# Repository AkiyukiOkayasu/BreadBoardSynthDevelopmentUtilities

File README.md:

# BreadBoardSynthDevelopmentUtilities  
[ブレッドボード　６穴版　ＥＩＣ－３９０１](https://akizukidenshi.com/catalog/g/gP-12366/)

## Eurorack power  
Pull the Eurorack's power bus cable out to the BreadBoard's power rail.  
Only split power lines in the middle can be used.  

## Pod

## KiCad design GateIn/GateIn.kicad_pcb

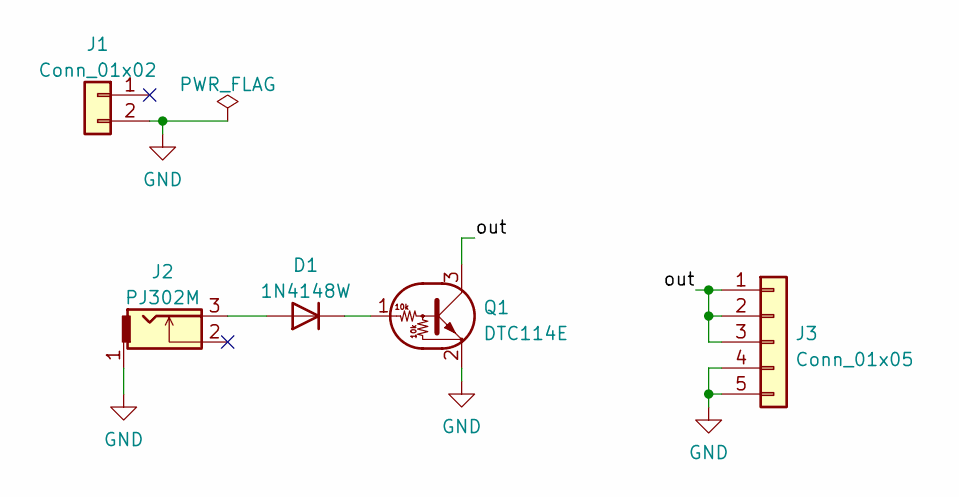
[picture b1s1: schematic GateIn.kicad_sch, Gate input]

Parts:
D1: 1N4148W; D_SOD-123
J1: Conn_01x02; PinHeader_1x02_P2.54mm_Vertical
J2: PJ302M
J3: Conn_01x05; PinHeader_1x05_P2.54mm_Vertical
Q1: DTC114E; SC-59_Handsoldering

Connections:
/out: J3.1, J3.2, J3.3, Q1.3 (C)
GND: J1.2, J2.1, J3.4, J3.5, Q1.2 (E)
unnamed: D1.1 (K), Q1.1 (B)
unnamed: D1.2 (A), J2.3

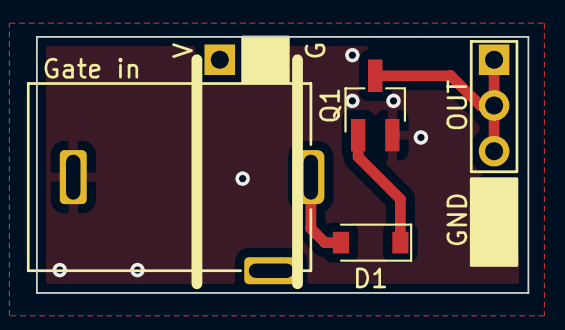
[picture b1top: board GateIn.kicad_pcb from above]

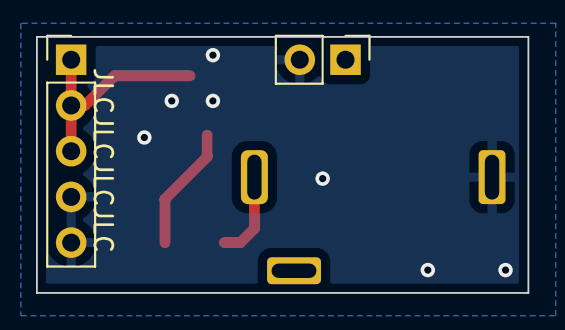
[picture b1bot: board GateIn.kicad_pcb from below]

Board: 2 copper layers, 27.3 x 14.2 mm, 5 parts (2 on the bottom side), 4 nets.

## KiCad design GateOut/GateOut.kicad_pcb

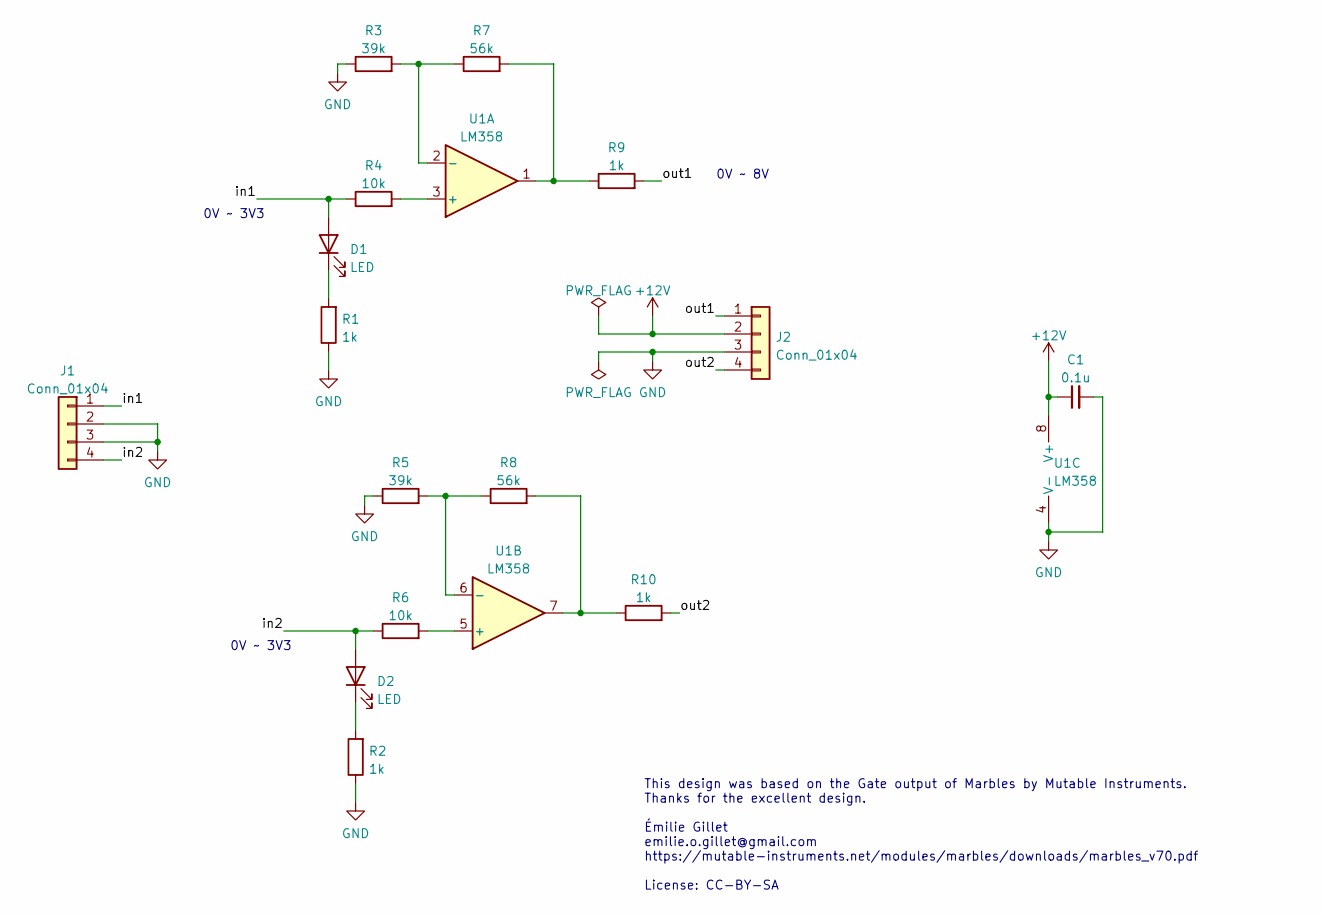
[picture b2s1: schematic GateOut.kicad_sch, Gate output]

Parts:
C1: 0.1u; C_0402_1005Metric_Pad0.74x0.62mm_HandSolder
D1, D2: LED; LED_0402_1005Metric_Pad0.77x0.64mm_HandSolder
J1, J2: Conn_01x04; PinHeader_1x04_P2.54mm_Vertical
R1, R2, R9, R10: 1k; R_0402_1005Metric_Pad0.72x0.64mm_HandSolder
R3, R5: 39k; R_0402_1005Metric_Pad0.72x0.64mm_HandSolder
R4, R6: 10k; R_0402_1005Metric_Pad0.72x0.64mm_HandSolder
R7, R8: 56k; R_0402_1005Metric_Pad0.72x0.64mm_HandSolder
U1: LM358; SOIC-8_3.9x4.9mm_P1.27mm

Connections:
+12V: C1.1, J2.2, U1.8 (V+)
/in1: D1.2 (A), J1.1, R4.1
/in2: D2.2 (A), J1.4, R6.1
/out1: J2.1, R9.2
/out2: J2.4, R10.2
GND: C1.2, J1.2, J1.3, J2.3, R1.1, R2.1, R3.1, R5.1, U1.4 (V-)
unnamed: D1.1 (K), R1.2
unnamed: D2.1 (K), R2.2
unnamed: R3.2, R7.1, U1.2 (-)
unnamed: R4.2, U1.3 (+)
unnamed: R5.2, R8.1, U1.6 (-)
unnamed: R6.2, U1.5 (+)
unnamed: R7.2, R9.1, U1.1
unnamed: R8.2, R10.1, U1.7

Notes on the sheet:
0V ~ 3V3
This design was based on the Gate output of Marbles by Mutable Instruments. Thanks for the excellent design. Émilie Gillet emilie.o.gillet@gmail.com https://mutable-instruments.net/modules/marbles/downloads/marbles_v70.pdf License: CC-BY-SA
0V ~ 8V

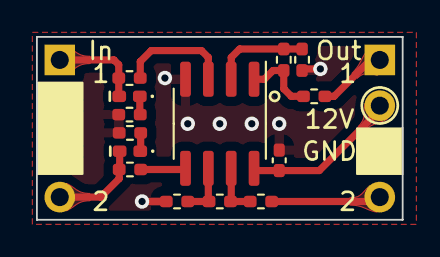
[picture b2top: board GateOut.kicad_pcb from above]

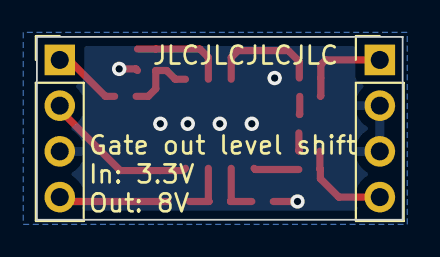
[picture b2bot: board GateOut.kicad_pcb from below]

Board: 2 copper layers, 20.3 x 10.2 mm, 16 parts (2 on the bottom side), 14 nets.

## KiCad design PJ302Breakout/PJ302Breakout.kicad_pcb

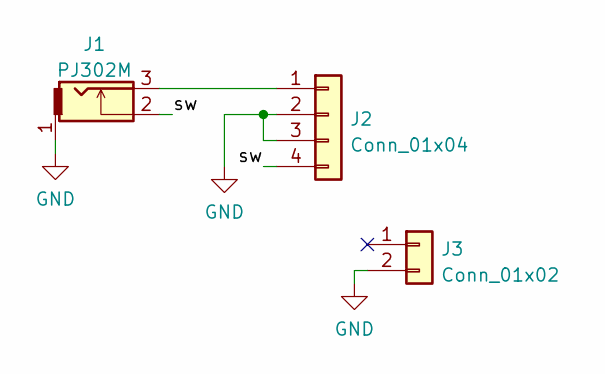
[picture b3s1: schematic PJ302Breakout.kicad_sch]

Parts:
J1: PJ302M
J2: Conn_01x04; PinHeader_1x04_P2.54mm_Vertical
J3: Conn_01x02; PinHeader_1x02_P2.54mm_Vertical

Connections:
/sw: J1.2, J2.4
GND: J1.1, J2.2, J2.3, J3.2
unnamed: J1.3, J2.1

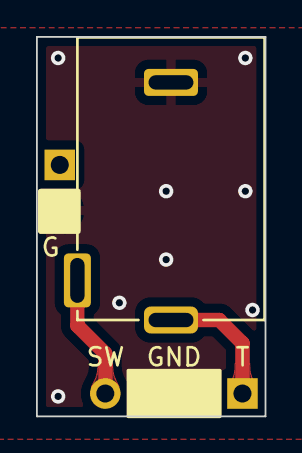
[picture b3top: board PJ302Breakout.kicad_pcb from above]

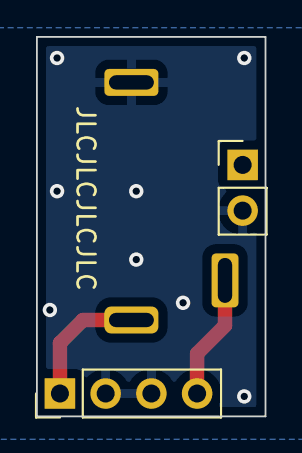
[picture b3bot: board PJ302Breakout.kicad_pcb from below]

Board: 2 copper layers, 12.7 x 21.1 mm, 3 parts (2 on the bottom side), 3 nets.

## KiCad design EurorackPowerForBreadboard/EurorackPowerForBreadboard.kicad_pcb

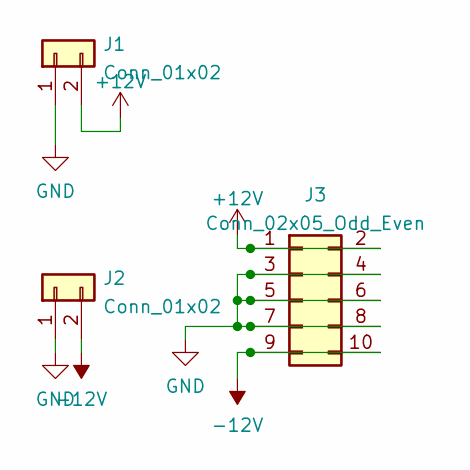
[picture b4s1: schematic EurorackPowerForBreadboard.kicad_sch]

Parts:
J1, J2: Conn_01x02; PinHeader_1x02_P2.54mm_Vertical
J3: Conn_02x05_Odd_Even; PinSocket_2x05_P2.54mm_Vertical

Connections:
+12V: J1.2, J3.1, J3.2
-12V: J2.2, J3.9, J3.10
GND: J1.1, J2.1, J3.3, J3.4, J3.5, J3.6, J3.7, J3.8

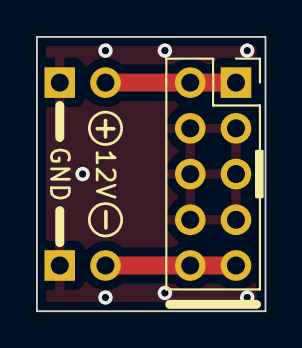
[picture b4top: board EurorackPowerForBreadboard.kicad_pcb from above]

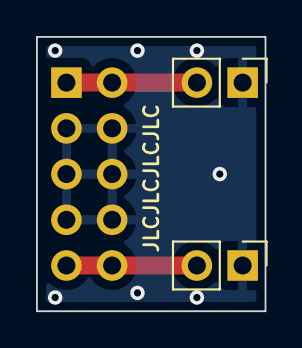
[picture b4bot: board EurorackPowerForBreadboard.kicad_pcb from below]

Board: 2 copper layers, 12.7 x 15.2 mm, 3 parts (2 on the bottom side), 3 nets.

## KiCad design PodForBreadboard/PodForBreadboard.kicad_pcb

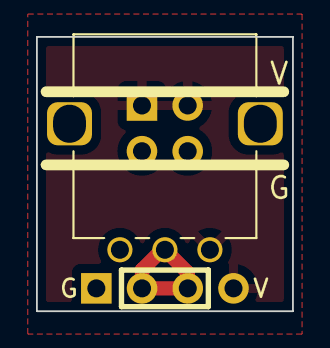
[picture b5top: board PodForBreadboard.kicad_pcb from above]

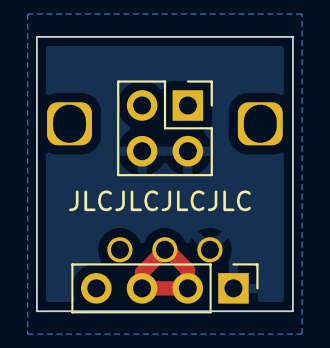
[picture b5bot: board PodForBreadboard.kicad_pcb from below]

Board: 2 copper layers, 14.2 x 15.2 mm, 3 parts (2 on the bottom side), 3 nets.

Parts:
J1: Conn_02x02_Odd_Even; PinHeader_2x02_P2.54mm_Vertical
J2: Conn_01x04; PinHeader_1x04_P2.54mm_Vertical
RV1: ALPS_RK09D; ALPS_RK09D117000B

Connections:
/2: J2.2, J2.3, RV1.2
GND: J1.2, J1.4, J2.1, RV1.1
VDD: J1.1, J1.3, J2.4, RV1.3

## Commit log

2022-02-21 gitignore
2022-02-21 EurorackPower
2022-02-21 Gerber
2022-02-21 ゾーンの再度塗りつぶし
2022-02-21 PJ302
2022-02-21 細かな調整
2022-02-25 PJ302 for BB
2022-02-25 Pod for BB
2022-03-02 Gate output level shifter
2022-03-03 GateOutのPCBのささかいな更新
2022-03-03 GateIn制作途中
